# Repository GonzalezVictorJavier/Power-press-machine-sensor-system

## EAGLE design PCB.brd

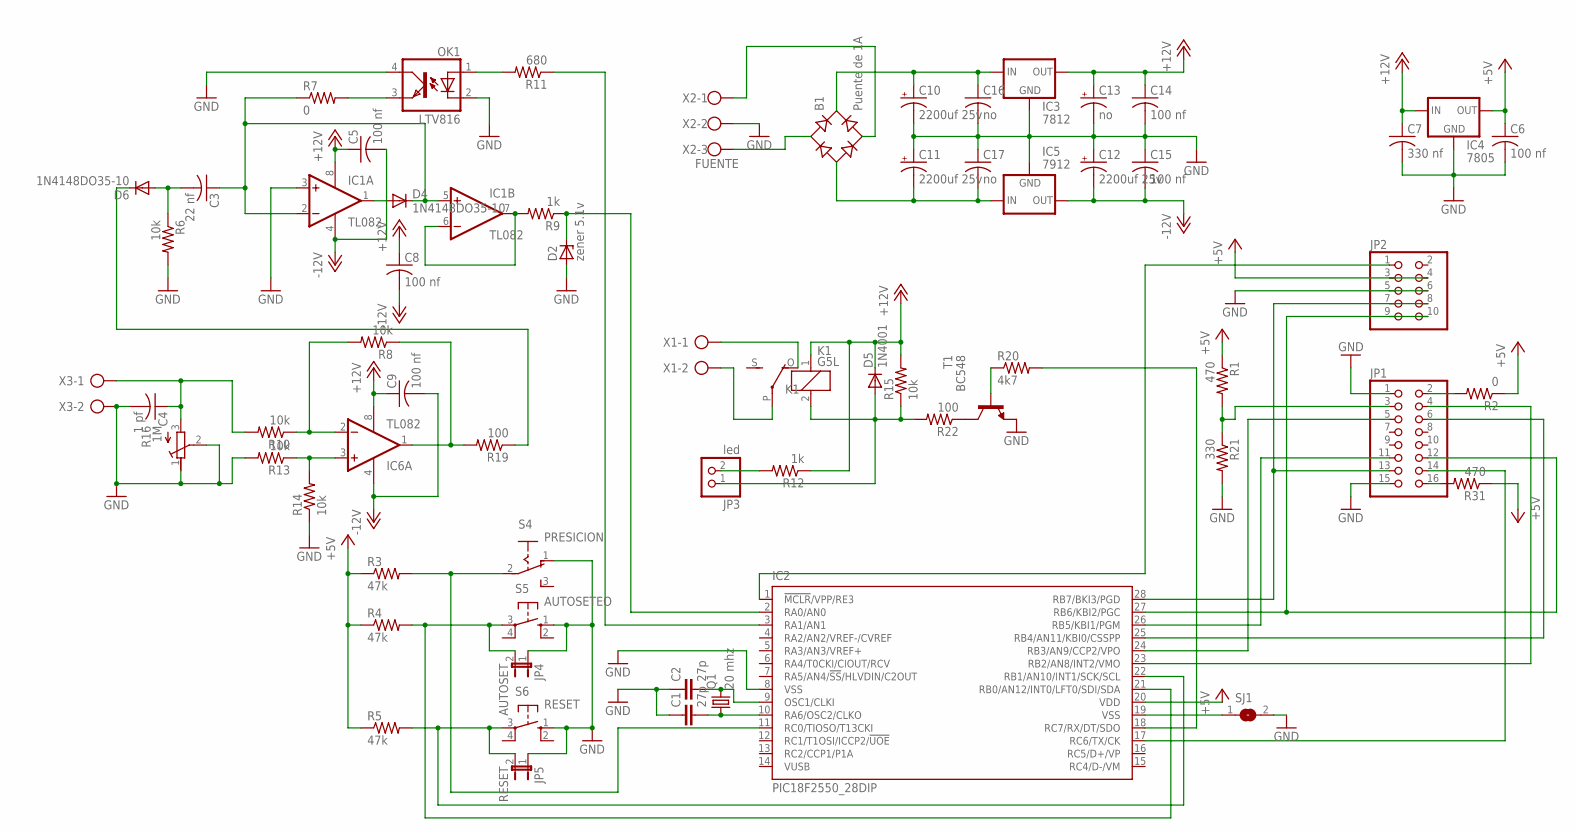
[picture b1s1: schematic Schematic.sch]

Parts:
B1: Puente de 1A; RB1A
C1, C2: 27p; C050-024X044
C3: 22 nf; C050-024X044
C4: 1 pf; C050-024X044
C5, C6, C8, C9, C14, C15: 100 nf; C050-024X044
C7: 330 nf; C050-024X044
C10, C11, C12: 2200uf 25v; E7,5-16
C13: no; E7,5-16
C16, C17: no; C050-024X044
D2: zener 5.1v; P1Z12
D4, D6: 1N4148DO35-10; DO35-10
D5: 1N4001; DO41-10
IC1, IC6: TL082; DIL08
IC2: PIC18F2550_28DIP; DIL28-3
IC3: 7812; 78XXS
IC4: 7805; 78XXS
IC5: 7912; 79XXS
JP1: PINHD-2X8; 2X08
JP2: PINHD-2X5; 2X05
JP3: led; 1X02
JP4: AUTOSET; JP1
JP5: RESET; JP1
K1: G5L; G5LE
OK1: LTV816; DIL04
Q1: 20 mhz; HC49/S
R1, R31: 470; 0207/10
R2, R7: 0; 0207/10
R3, R4, R5: 47k; 0207/10
R6, R8, R10, R13, R14, R15: 10k; 0207/10
R9, R12: 1k; 0207/10
R11: 680; 0207/10
R16: 1M; RTRIMT93YA
R19, R22: 100; 0207/10
R20: 4k7; 0207/10
R21: 330; 0207/10
S4: PRESICION; M251
S5: AUTOSETEO; B3F-10XX
S6: RESET; B3F-10XX
SJ1: SJ
T1: BC548; TO92
X1, X3: AK300/2
X2: FUENTE; W237-103

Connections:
+5V: C6.1, IC2.20 (VDD), IC4.OUT, JP2.3, JP2.4, R1.1, R2.1, R3.1, R4.1, R5.1, R31.1
+12V: C5.1, C7.1, C8.1, C9.1, C13.+, C14.1, D5.C, IC1.8 (V+), IC3.OUT, IC4.IN, IC6.8 (V+), K1.1, R12.1, R15.2
-12V: C5.2, C8.2, C9.2, C12.-, C15.2, IC1.4 (V-), IC5.OUT, IC6.4 (V-)
GND: C1.1, C2.1, C4.2, C6.2, C7.2, C10.-, C11.+, C12.+, C13.-, C14.2, C15.1, C16.2, C17.1, D2.A, IC1.3 (+IN), IC2.8 (VSS), IC3.GND, IC4.GND, IC5.GND, JP1.1, JP1.15, JP2.5, JP2.6, JP4.1, JP5.1, OK1.2 (C), OK1.4 (COL), R6.2, R13.2, R14.1, R16.1 (A), R16.2 (S), R21.2, S4.1 (O), S5.1 (S), S6.1 (S), SJ1.2, T1.1 (E), X2.2, X3.2
unnamed: IC6.3 (+IN), R13.1, R14.2
unnamed: JP1.3, R1.2, R21.1
unnamed: D6.C, R19.1
unnamed: JP1.2, R2.2
unnamed: JP1.16, R31.2
unnamed: C3.2, D6.A, R6.1
unnamed: IC6.2 (-IN), R8.2, R10.1
unnamed: IC2.23 (RB2/AN8/INT2/VMO), JP1.4
unnamed: IC2.24 (RB3/AN9/CCP2/VPO), JP1.5
unnamed: IC2.25 (RB4/AN11/KBI0/CSSPP), JP1.6
unnamed: IC2.26 (RB5/KBI1/PGM), JP1.11
unnamed: IC2.27 (RB6/KBI2/PGC), JP1.12, JP2.9, JP2.10
unnamed: IC2.11 (RC0/TIOSO/T13CKI), R3.2, S4.2
unnamed: IC2.21 (RB0/AN12/INT0/LFT0/SDI/SDA), JP4.2, R4.2, S5.3
unnamed: IC2.22 (RB1/AN10/INT1/SCK/SCL), JP5.2, R5.2, S6.3
unnamed: JP3.2, R12.2
unnamed: IC2.28 (RB7/BKI3/PGD), JP1.13, JP2.7, JP2.8
unnamed: IC2.19 (VSS), SJ1.1
unnamed: IC2.17 (RC6/TX/CK), JP1.14
unnamed: C3.1, D4.C, IC1.2 (-IN), IC1.5 (+IN), R7.1
unnamed: IC6.1 (OUT), R8.1, R19.2
unnamed: D4.A, IC1.1 (OUT)
unnamed: IC2.1 (!MCLR!/VPP/RE3), JP2.1
unnamed: C2.2, IC2.9 (OSC1/CLKI), Q1.2
unnamed: C1.2, IC2.10 (RA6/OSC2/CLKO), Q1.1
unnamed: B1.+, C10.+, C16.1, IC3.IN
unnamed: OK1.1 (A), R11.2
unnamed: OK1.3 (EMIT), R7.2
unnamed: IC1.6 (-IN), IC1.7 (OUT), R9.2
unnamed: K1.P, X1.2
unnamed: B1.-, C11.-, C17.2, IC5.IN
unnamed: B1.AC2, X2.1
unnamed: B1.AC1, X2.3
unnamed: K1.O, X1.1
unnamed: IC2.18 (RC7/RX/DT/SDO), R20.2
unnamed: D5.A, JP3.1, K1.2, R15.1, R22.2
unnamed: D2.C, IC2.2 (RA0/AN0), R9.1
unnamed: IC2.3 (RA1/AN1), R11.1
unnamed: R22.1, T1.3 (C)
unnamed: C4.1, R10.2, R16.3 (E), X3.1
unnamed: R20.1, T1.2 (B)

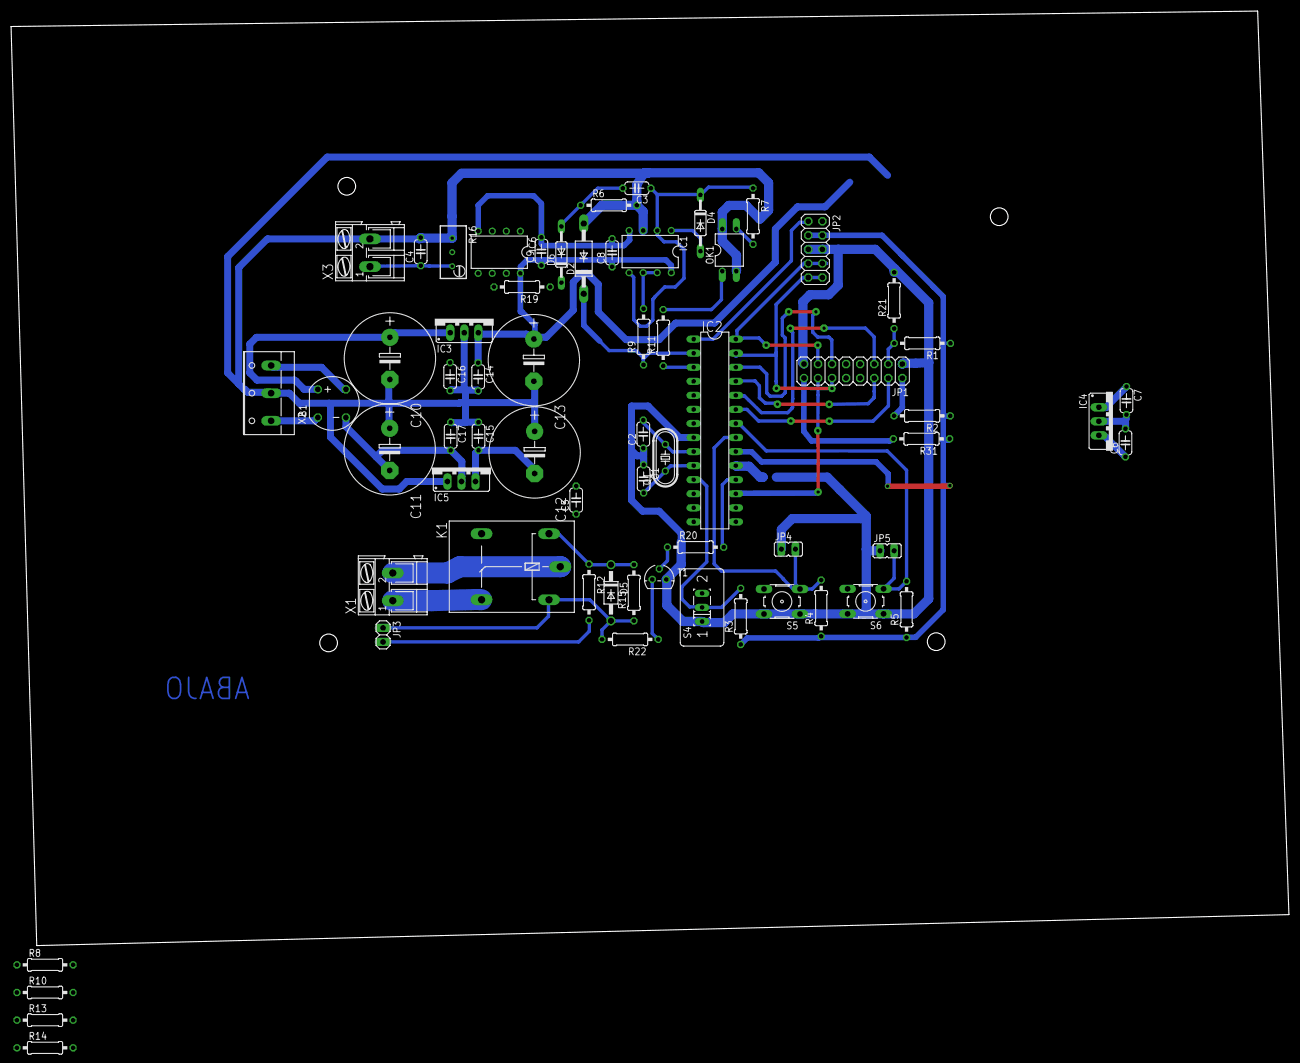
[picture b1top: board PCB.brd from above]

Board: 2 copper layers, 231.0 x 168.9 mm, 65 parts (1 on the bottom side), 45 nets.

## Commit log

2021-12-21 First ver
    The machine is working.
    Algorithm: Noise test.
    Board and scheme: I finally decide to use the TL082 opamp.
2021-12-21 Ver 2
    Algorithm: I applied some filters.
    Board and scheme: I implemented a balanced opamp circuit that proof to by less noisy.
2021-12-21 Update Pic18f2550 code.c
    Algorithm: Change some variable types to DOUBLE that increased the accuracy.
    Finally, the MCLR function wasn't useful, so i toke it away.
